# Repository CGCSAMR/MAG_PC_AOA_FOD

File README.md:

# MAG_PC_AOA_FOD
 Magnetometer, Particle Counter, Angle Of Arrival and FemtoSatellite deploy and implementation  for PC 104 Standard
 
 Link para llenar lista de componentes (Basado en nomenclatura del Documento Sheets.pdf y el proyecto)
 https://docs.google.com/spreadsheets/d/1CENiZx1N7Sxhc1uEzrNK5IoRTlJ-0vuplnp879NBSzI/edit?usp=sharing

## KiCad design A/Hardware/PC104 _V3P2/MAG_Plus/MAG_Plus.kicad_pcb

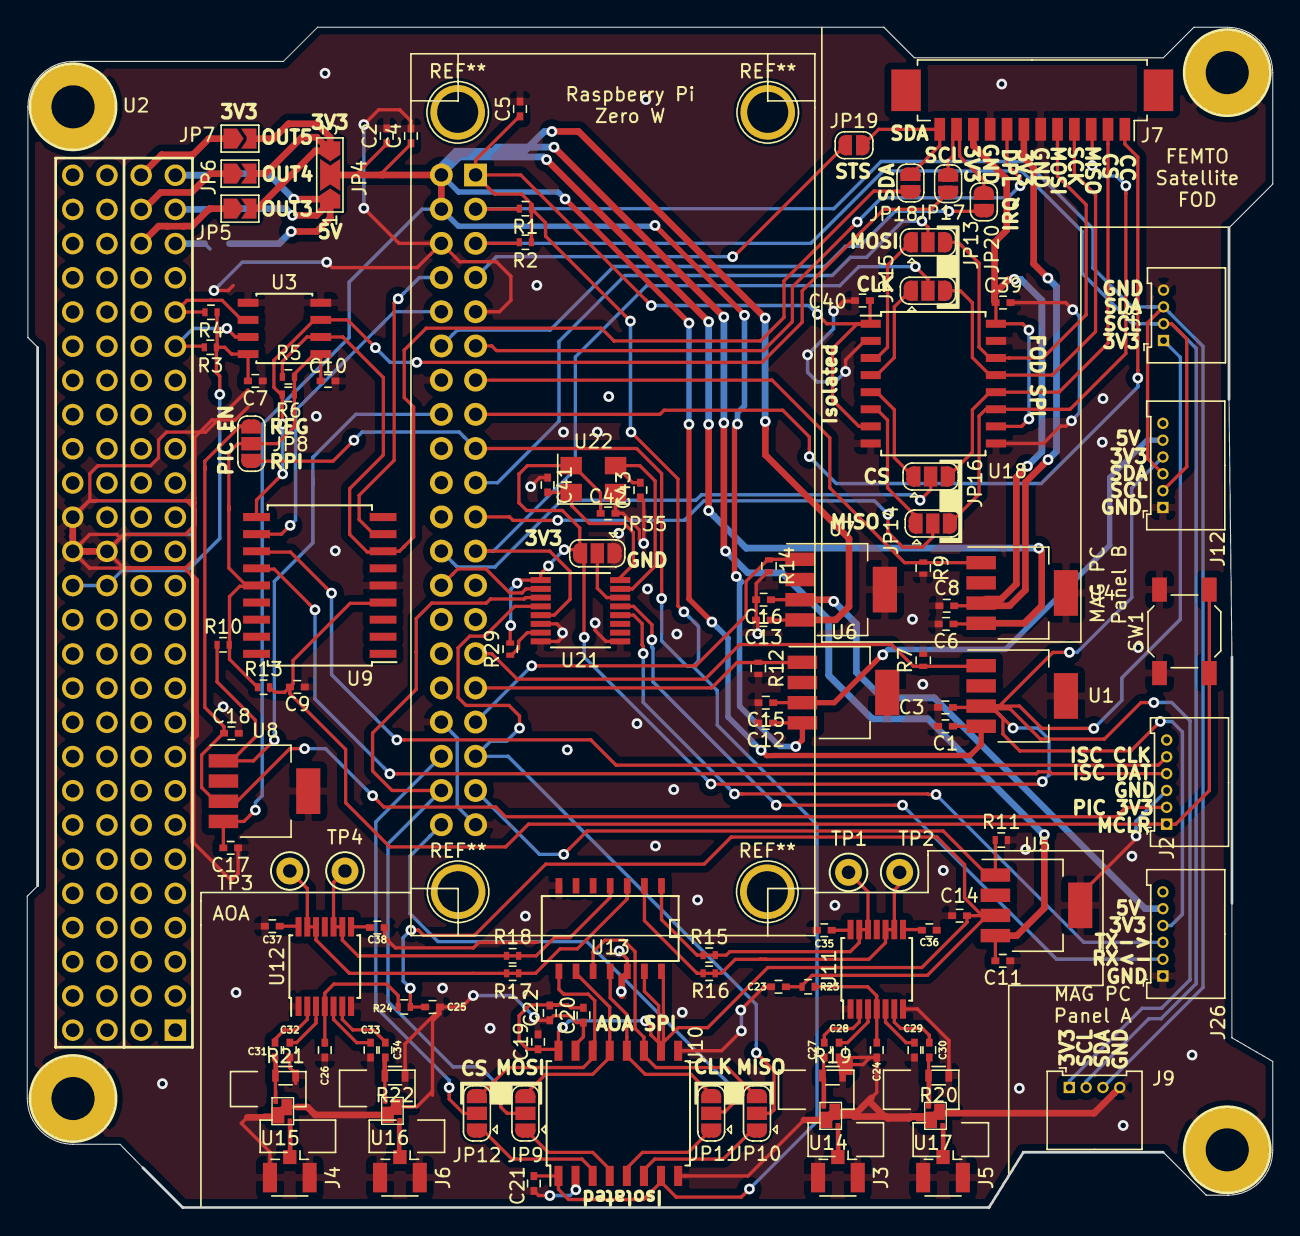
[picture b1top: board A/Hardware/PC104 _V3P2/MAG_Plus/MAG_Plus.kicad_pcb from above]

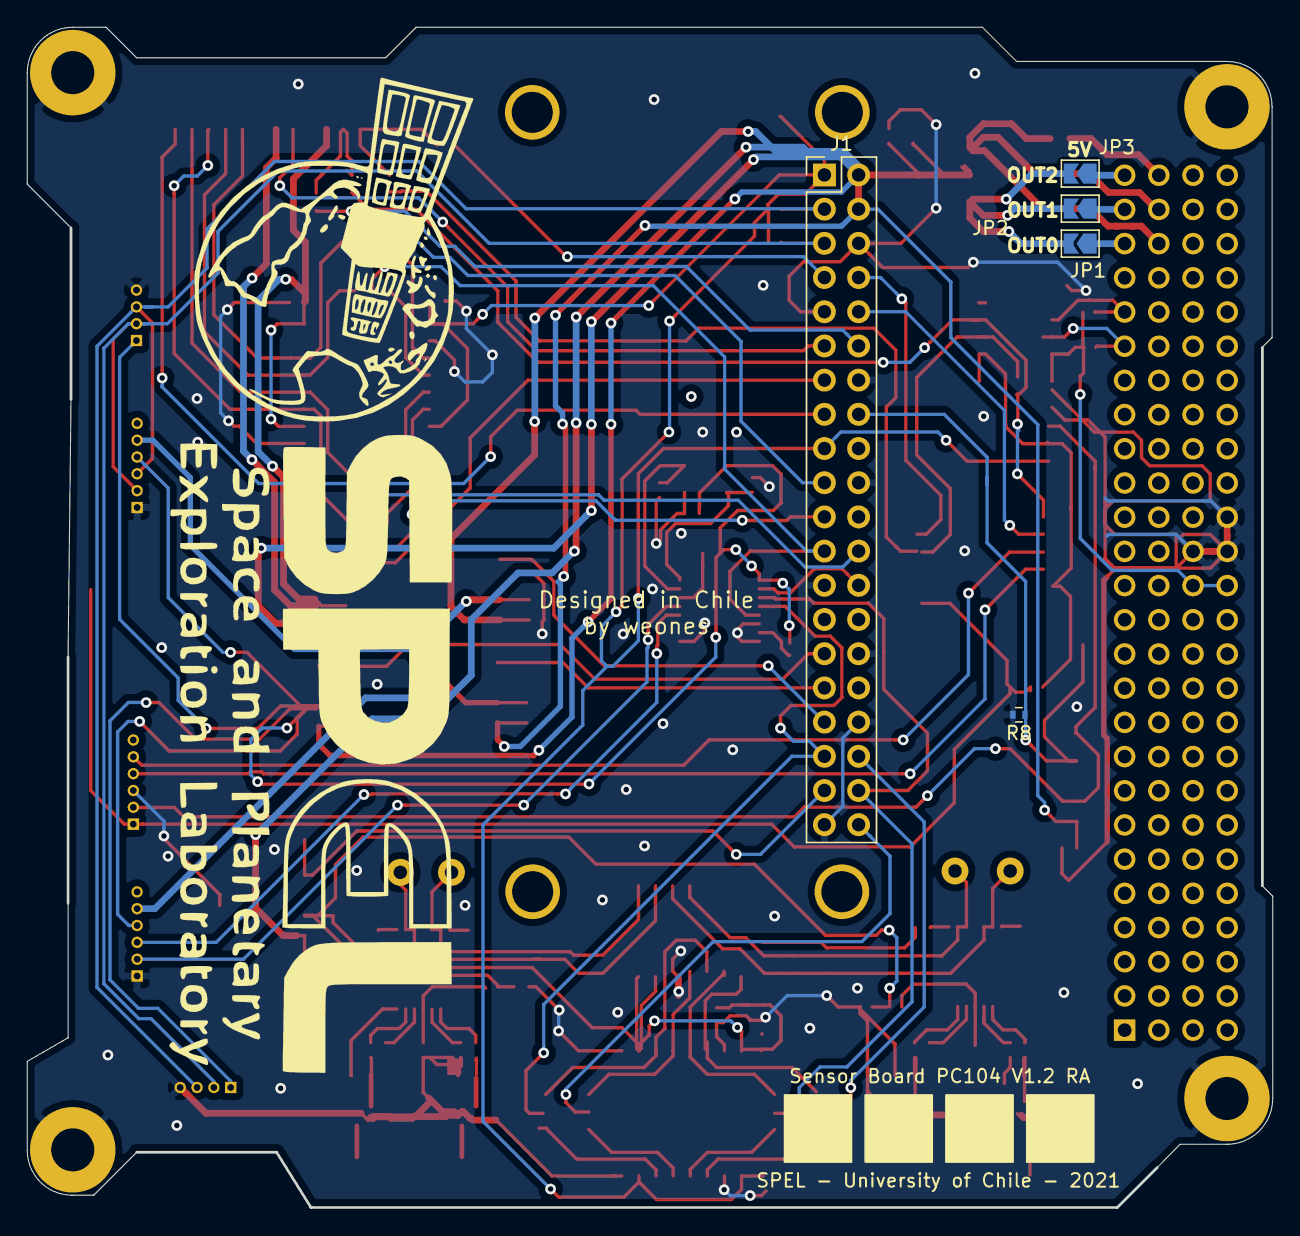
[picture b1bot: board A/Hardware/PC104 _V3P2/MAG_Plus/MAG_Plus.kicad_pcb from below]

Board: 2 copper layers, 92.5 x 87.7 mm, 125 parts (5 on the bottom side), 99 nets.

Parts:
C1, C2, C3, C4, C5, C6, C7, C8, C9, C10, C11, C12, C13, C14, C15, C16, C17, C18, C19, C20, C21, C22, C39, C40, C42: C; C_0402
C23, C24, C25, C26, C27, C28, C29, C30, C31, C32, C33, C34, C35, C36, C37, C38: C_Small; C_0402
C41, C43: 15pF; C_0402
J1: RPi_GPIO; Pin_Header_Straight_2x20_Pitch2.54mm
J2, J12, J26: Conn_01x06_Male; Molex_PicoBlade_53048-0610_06x1.25mm_Angled
J3, J4, J5, J6: U.FL-R-SMT(01); U.FL_Hirose_U.FL-R-SMT-1_Vertical
J7: Conn_01x12_Male; Molex_PicoBlade_53261-1271_12x1.25mm_Angled
J8, J9: Conn_01x04_Male; Molex_PicoBlade_53048-0410_04x1.25mm_Angled
JP1, JP2, JP3, JP5, JP6, JP7: Jumper_2_Open; SolderJumper-2_P1.3mm_Open_TrianglePad1.0x1.5mm
JP4: Jumper_3_Open; SolderJumper-3_P2.0mm_Open_TrianglePad1.0x1.5mm_NumberLabels
JP8, JP9, JP10, JP11, JP12, JP13, JP14, JP15, JP16: Jumper_3_Open; SolderJumper-3_P1.3mm_Open_RoundedPad1.0x1.5mm
JP17, JP18, JP19, JP20: Jumper_2_Open; SolderJumper-2_P1.3mm_Open_RoundedPad1.0x1.5mm
JP35: SolderJumper_3_Open; SolderJumper-3_P1.3mm_Open_RoundedPad1.0x1.5mm
R1, R2, R3, R4, R5, R6, R7, R8, R9, R10, R11, R12, R13, R14, R15, R16, R17, R18, R29: R; R_0402
R19, R20, R21, R22: R_Small; R_0603
R23, R24: R_Small; R_0402
SW1: SW_Push; SW_SPST_SKQG
TP1, TP2, TP3, TP4: TestPoint; Test_Point_Keystone_5000-5004_Miniature
U1, U4, U8: LP38693MP-3.3; SOT-223-5
U2: Payload; PC104-Standard
U3: ISO1540; SOIC-8_3.9x4.9mm_Pitch1.27mm
U5, U6, U7: LP38693MP-5.0; SOT-223-5
U9: PIC16F1847-I_SO; SOIC-18W_7.5x11.6mm_Pitch1.27mm
U10, U18: ISO7341C; SOIC-16W_7.5x10.3mm_Pitch1.27mm
U11, U12: AD8302; TSSOP-14_4.4x5mm_Pitch0.65mm
U13: MCP3204; SOIC-14_N
U14, U15, U16, U17: QPQ1906SR; QPQ1906SR3
U21: SC16IS741AIPWJ; TSSOP-16_4.4x5mm_Pitch0.65mm
U22: Xtal; Crystal_SMD_5032-4pin_5.0x3.2mm

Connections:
3V3IN: JP1.2, JP2.2, JP3.2, JP4.1
5VIN: JP4.3, JP5.2, JP6.2, JP7.2
ANT1_IN: J3.1, U14.1
ANT1_OUT: C27.1, R19.1, U14.2
ANT2_IN: J5.1, U17.1
ANT2_OUT: C30.1, R20.2, U17.2
ANT3_IN: J4.1, U15.1
ANT3_OUT: C31.1, R21.1, U15.2
ANT4_IN: J6.1, U16.1
ANT4_OUT: C34.1, R22.2, U16.2
AOA_5V: C14.1, C19.1, C20.1, C22.1, C23.2, C25.2, R23.1, R24.1, U5.3, U10.10, U10.16, U13.13, U13.14
AOA_CLK: JP11.3, U10.12, U13.11
AOA_EN: J1.37, R11.1, U5.1
AOA_MISO: JP10.3, U10.11, U13.10
AOA_MOSI: JP9.3, U10.13, U13.9
AOA_SS: JP12.3, U10.14, U13.8
CLK0: J1.23, JP15.2, U21.5
CLK1: J1.40, JP11.2
CSP_SCL: R4.2, U2.43, U3.6
CSP_SDA: R3.2, U2.41, U3.7
FOD_3V3: C8.1, C39.1, J7.7, J7.10, U4.3, U18.10, U18.16
FOD_CC: J1.15, J7.1
FOD_CS: J7.2, JP16.3, U18.12
FOD_DPL: J1.11, J7.8
FOD_EN: J1.13, R9.1, U4.1
FOD_IRQ: J1.12, JP20.1
FOD_MISO: J7.3, JP14.3, U18.11
FOD_MOSI: J7.5, JP13.3, U18.14
FOD_SCK: J7.4, JP15.3, U18.13
FOD_SCL: J7.11, JP17.2, JP20.2
FOD_SDA: J7.12, JP18.2, JP19.2
FOD_STS: J1.7, JP19.1
GND: C1.2, C2.2, C3.2, C4.2, C5.2, C6.2, C7.2, C8.2, C9.1, C10.2, C11.2, C12.2, C13.2, C14.2, C15.2, C16.2, C17.2, C18.2, C19.2, C20.2, C21.2, C22.2, C23.1, C24.1, C25.1, C26.1, C28.1, C29.1, C32.1, C33.1, C35.2, C36.2, C37.2, C38.2, C39.2, C40.2, C41.1, C42.2, C43.1, J1.6, J1.9, J1.14, J1.20, J1.25, J1.30, J1.34, J1.39, J2.3, J3.2, J4.2, J5.2, J6.2, J7.6, J7.9, J8.4, J9.4, J12.1, J26.1, JP35.1, R7.2, R8.2, R9.2, R11.2, R12.2, R14.2, R19.2, R20.1, R21.2, R22.1, SW1.1, U1.5, U2.81, U2.82, U2.84, U3.4, U3.5, U4.5, U5.5, U6.5, U7.5, U8.5, U9.5, U10.2, U10.8, U10.9, U10.15, U11.1, U11.7, U12.1, U12.7, U13.7, U13.12, U14.3, U15.3, U16.3, U17.3, U18.2, U18.8, U18.9, U18.15, U21.6, U21.8, U21.9, U22.2
ICSPCLK: J2.5, U9.12
ICSPDAT: J2.4, U9.13
IRQ: R29.1, U21.7
LP_5V: C16.1, J26.5, U7.3
LP_EN: J1.33, R14.1, U7.1
LP_RESET: JP35.2, U21.14
MAG_3V3: C3.1, C42.1, J8.1, J9.1, J12.4, J26.4, JP35.3, R29.2, U1.3, U21.1, U22.4
MAG_EN: J1.29, R7.1, U1.1
MCLR: C9.2, J2.1, R13.2, SW1.2, U9.4
MISO0: J1.21, JP14.2
MISO1: J1.35, JP10.2, U21.4
MOSI0: J1.19, JP13.2
MOSI1: J1.38, JP9.2, U21.3
unnamed: C24.2, R23.2, U11.4
unnamed: C26.2, R24.2, U12.4
unnamed: C27.2, U11.2
unnamed: C28.2, U11.3
unnamed: C29.2, U11.5
unnamed: C30.2, U11.6
unnamed: C31.2, U12.2
unnamed: C32.2, U12.3
unnamed: C33.2, U12.5
unnamed: C34.2, U12.6
unnamed: C35.1, U11.14
unnamed: C36.1, U11.8
unnamed: C37.1, U12.14
unnamed: C38.1, U12.8
OUT1_3V3: JP1.1, U2.47
OUT2_3V3: JP2.1, U2.49
OUT3_3V3: JP3.1, U2.51
OUT4_5V0: JP5.1, U2.48
OUT5_5V0: JP6.1, U2.50
OUT6_5V0: JP7.1, U2.52
PC_5V: C15.1, J12.5, U6.3
PC_EN: J1.31, R12.1, U6.1
PIC_3V3: C18.1, J2.2, JP8.1, U8.3
PIC_3V3J: C10.1, JP8.2, R5.1, R6.1, R10.2, R13.1, U3.1, U9.14
PIC_EN: J1.16, R8.1, R10.1, U8.1
PIC_SCL: JP17.1, R6.2, U3.3, U9.10
PIC_SDA: JP18.1, R5.2, U3.2, U9.7
RPI_3V3: C5.1, C21.1, C40.1, J1.1, J1.17, JP8.3, R1.1, R2.1, U10.1, U10.7, U18.1, U18.7
RPI_RX: J1.10, U9.11
RPI_SCL: J1.5, J8.2, J9.2, J12.2, R2.2
RPI_SDA: J1.3, J8.3, J9.3, J12.3, R1.2
RPI_TX: J1.8, U9.8
RX: J26.2, U21.13
SAT_3V3: C7.1, R3.1, R4.1, U2.79, U2.80, U3.8
SS00: J1.24, JP16.2
SS01: J1.26, U21.2
SS10: J1.36, JP12.2
TX: J26.3, U21.12
VIN: C1.1, C2.1, C4.1, C6.1, C11.1, C12.1, C13.1, C17.1, J1.2, J1.4, JP4.2, U1.4, U4.4, U5.4, U6.4, U7.4, U8.4
VMAG1: R15.1, R15.2, TP1.1, U11.12, U11.13, U13.1
VMAG2: R17.1, R17.2, TP3.1, U12.12, U12.13, U13.3
VPHS1: R16.1, R16.2, TP2.1, U11.9, U11.10, U13.2
VPHS2: R18.1, R18.2, TP4.1, U12.9, U12.10, U13.4
XTAL1: C43.2, U22.3
XTAL2: C41.2, U22.1
iaRPI_CLK: JP11.1, U10.5
iaRPI_MISO: JP10.1, U10.6
iaRPI_MOSI: JP9.1, U10.4
iaRPI_SS0: JP12.1, U10.3
ifRPI_CLK: JP15.1, U18.4
ifRPI_MISO: JP14.1, U18.6
ifRPI_MOSI: JP13.1, U18.3
ifRPI_SS0: JP16.1, U18.5

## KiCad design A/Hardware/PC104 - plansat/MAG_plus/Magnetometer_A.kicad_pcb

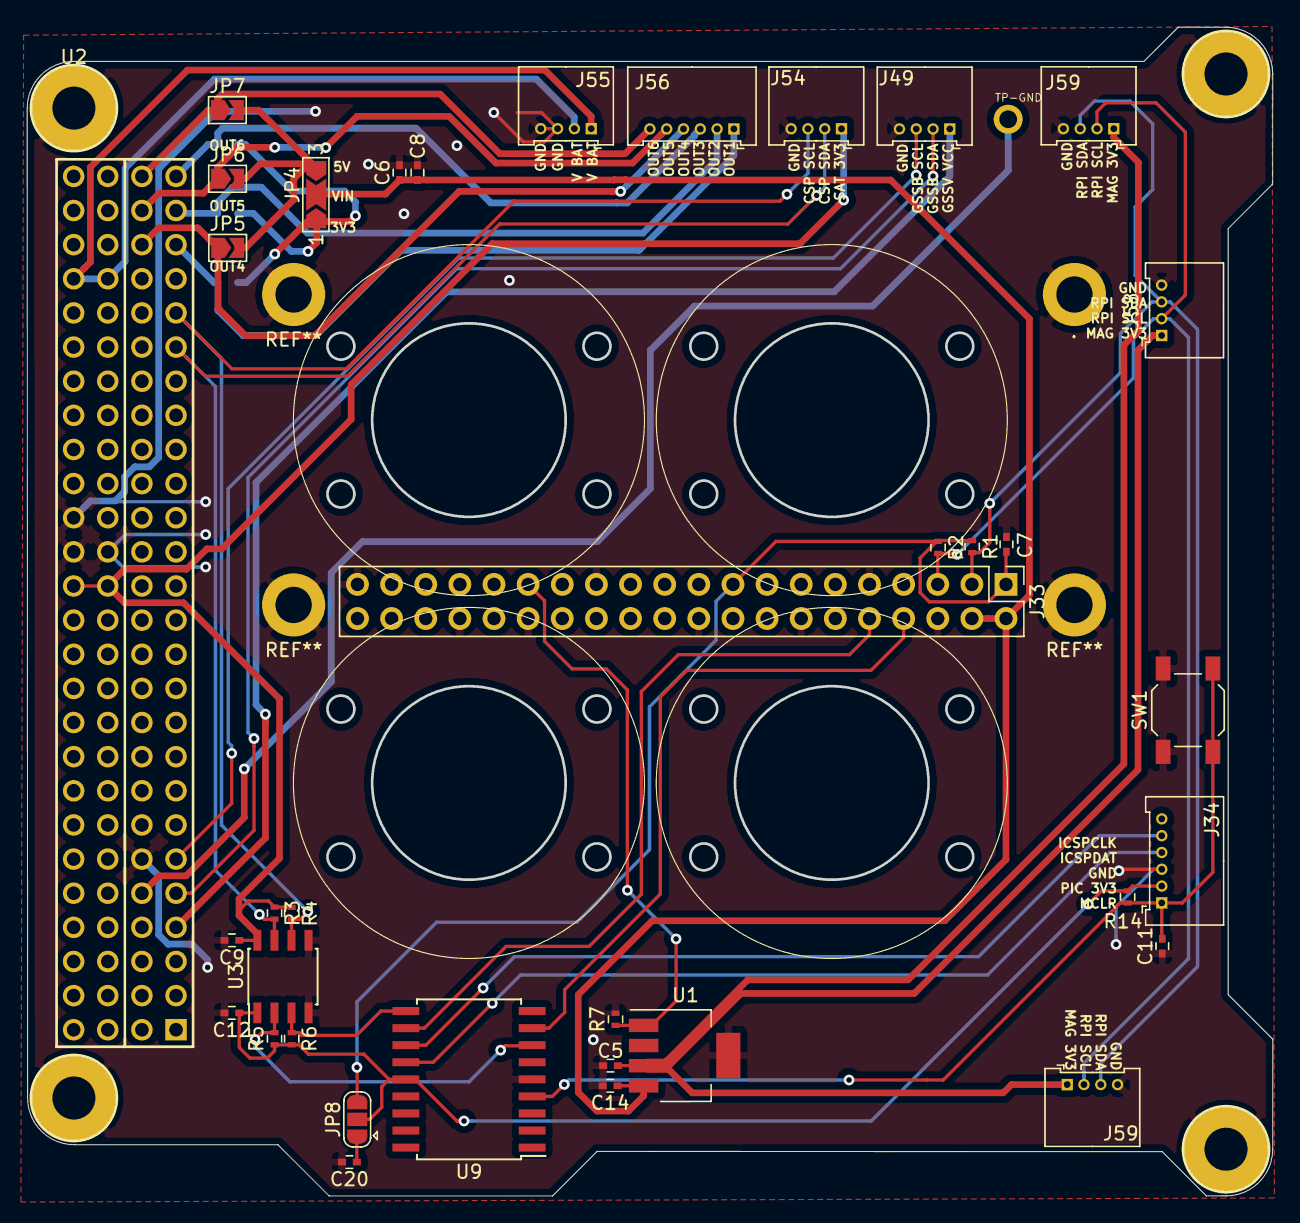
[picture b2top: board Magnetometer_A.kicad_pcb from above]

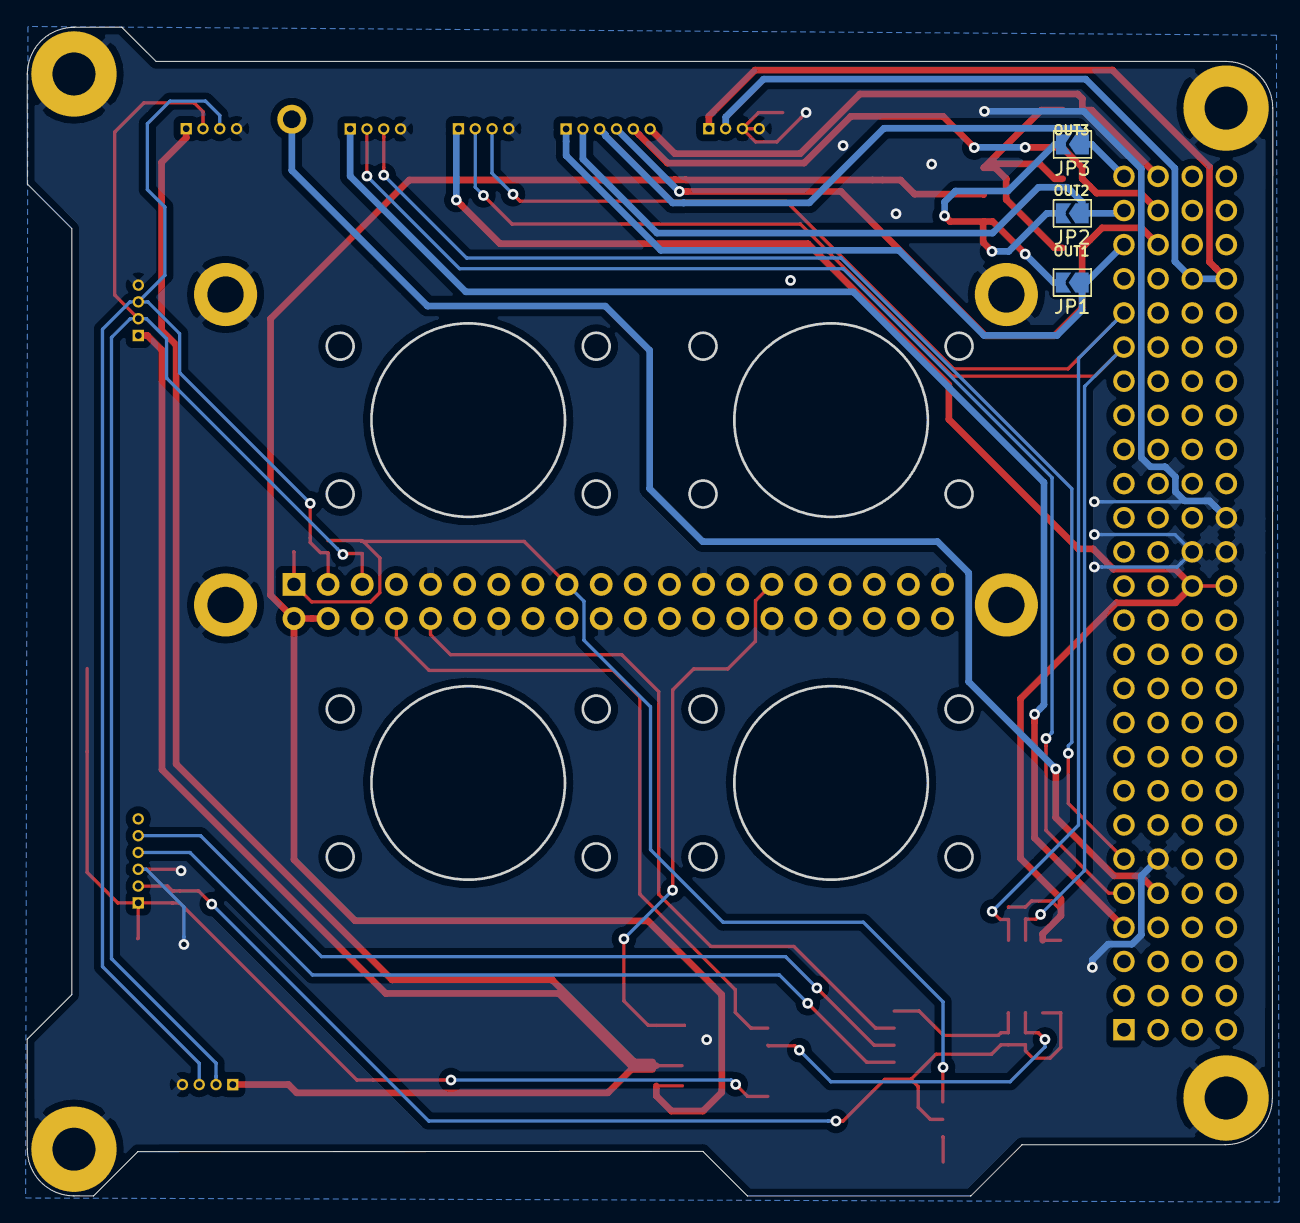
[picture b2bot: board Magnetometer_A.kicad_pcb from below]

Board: 2 copper layers, 92.7 x 87.0 mm, 41 parts (3 on the bottom side), 32 nets.

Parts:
.: MountingHole_2.7mm_M2.5_DIN965_Pad
C5, C6, C7, C8, C9, C11, C12, C14, C20: C; C_0402
J33: RPi_GPIO; Pin_Header_Straight_2x20_Pitch2.54mm
J34: Conn_01x06_Male; Molex_PicoBlade_53048-0610_06x1.25mm_Angled
J49, J54, J55: Conn_01x04_Female; Molex_PicoBlade_53048-0410_04x1.25mm_Angled
J56: Conn_01x06_Female; Molex_PicoBlade_53048-0610_06x1.25mm_Angled
J58, J59, J59#2: Conn_01x04_Male; Molex_PicoBlade_53048-0410_04x1.25mm_Angled
JP1, JP2, JP3, JP5, JP6, JP7: Jumper_2_Open; SolderJumper-2_P1.3mm_Open_TrianglePad1.0x1.5mm
JP4: Jumper_3_Open; SolderJumper-3_P2.0mm_Open_TrianglePad1.0x1.5mm_NumberLabels
JP8: Jumper_3_Open; SolderJumper-3_P1.3mm_Open_RoundedPad1.0x1.5mm
R1, R2, R3, R4, R5, R6, R7, R14: R; R_0402
SW1: SW_Push; SW_SPST_SKQG
TP-GND: PTR1PAD1-13; P1-13
U1: LP38693MP-3.3; SOT-223-5
U2: Payload; PC104-Standard
U3: ISO1540; SOIC-8_3.9x4.9mm_Pitch1.27mm
U9: PIC16F1847-I_SO; SOIC-18W_7.5x11.6mm_Pitch1.27mm

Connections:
3V3IN: JP1.2, JP2.2, JP3.2, JP4.1
5VIN: JP4.3, JP5.2, JP6.2, JP7.2
CSP_SCL: J54.3, R4.2, U2.43, U3.6
CSP_SDA: J54.2, R3.2, U2.41, U3.7
GND: ..1, C5.2, C6.2, C7.2, C8.2, C9.2, C11.1, C12.2, C14.2, C20.2, J33.6, J33.9, J33.14, J33.20, J33.25, J33.30, J33.34, J33.39, J34.3, J49.4, J54.4, J55.3, J55.4, J58.4, J59.4, J59#2.4, R7.2, SW1.1, U1.5, U2.12, U2.81, U2.82, U2.84, U3.4, U3.5, U9.5
GSSB_SCL: J49.3, U2.11
GSSB_SDA: J49.2, U2.9
GSSB_VCC: J49.1, U2.7
ICSPCLK: J34.5, U9.12
ICSPDAT: J34.4, U9.13
MAG_3V3: C5.1, J58.1, J59.1, J59#2.1, U1.3
MAG_EN: J33.29, R7.1, U1.1
MCLR: C11.2, J34.1, R14.2, SW1.2, U9.4
unnamed: TP-GND.TP, U2.10
OUT1_3V3: J56.1, JP1.1, U2.47
OUT2_3V3: J56.2, JP2.1, U2.49
OUT3_3V3: J56.3, JP3.1, U2.51
OUT4_5V0: J56.4, JP5.1, U2.48
OUT5_5V0: J56.5, JP6.1, U2.50
OUT6_5V0: J56.6, JP7.1, U2.52
PIC_3V3: C20.1, JP8.1
PIC_3V3J: C12.1, J34.2, JP8.2, R5.1, R6.1, R14.1, U3.1, U9.14
PIC_SCL: R6.2, U3.3, U9.10
PIC_SDA: R5.2, U3.2, U9.7
RPI_3V3: C7.1, J33.1, J33.17, JP8.3, R1.1, R2.1
RPI_RX: J33.10, U9.11
RPI_SCL: J33.5, J58.2, J59.2, J59#2.2, R2.2
RPI_SDA: J33.3, J58.3, J59.3, J59#2.3, R1.2
RPI_TX: J33.8, U9.8
SAT_3V3: C9.1, J54.1, R3.1, R4.1, U2.79, U2.80, U3.8
VIN: C6.1, C8.1, C14.1, J33.2, J33.4, JP4.2, U1.4
V_BAT: J55.1, J55.2, U2.97, U2.98

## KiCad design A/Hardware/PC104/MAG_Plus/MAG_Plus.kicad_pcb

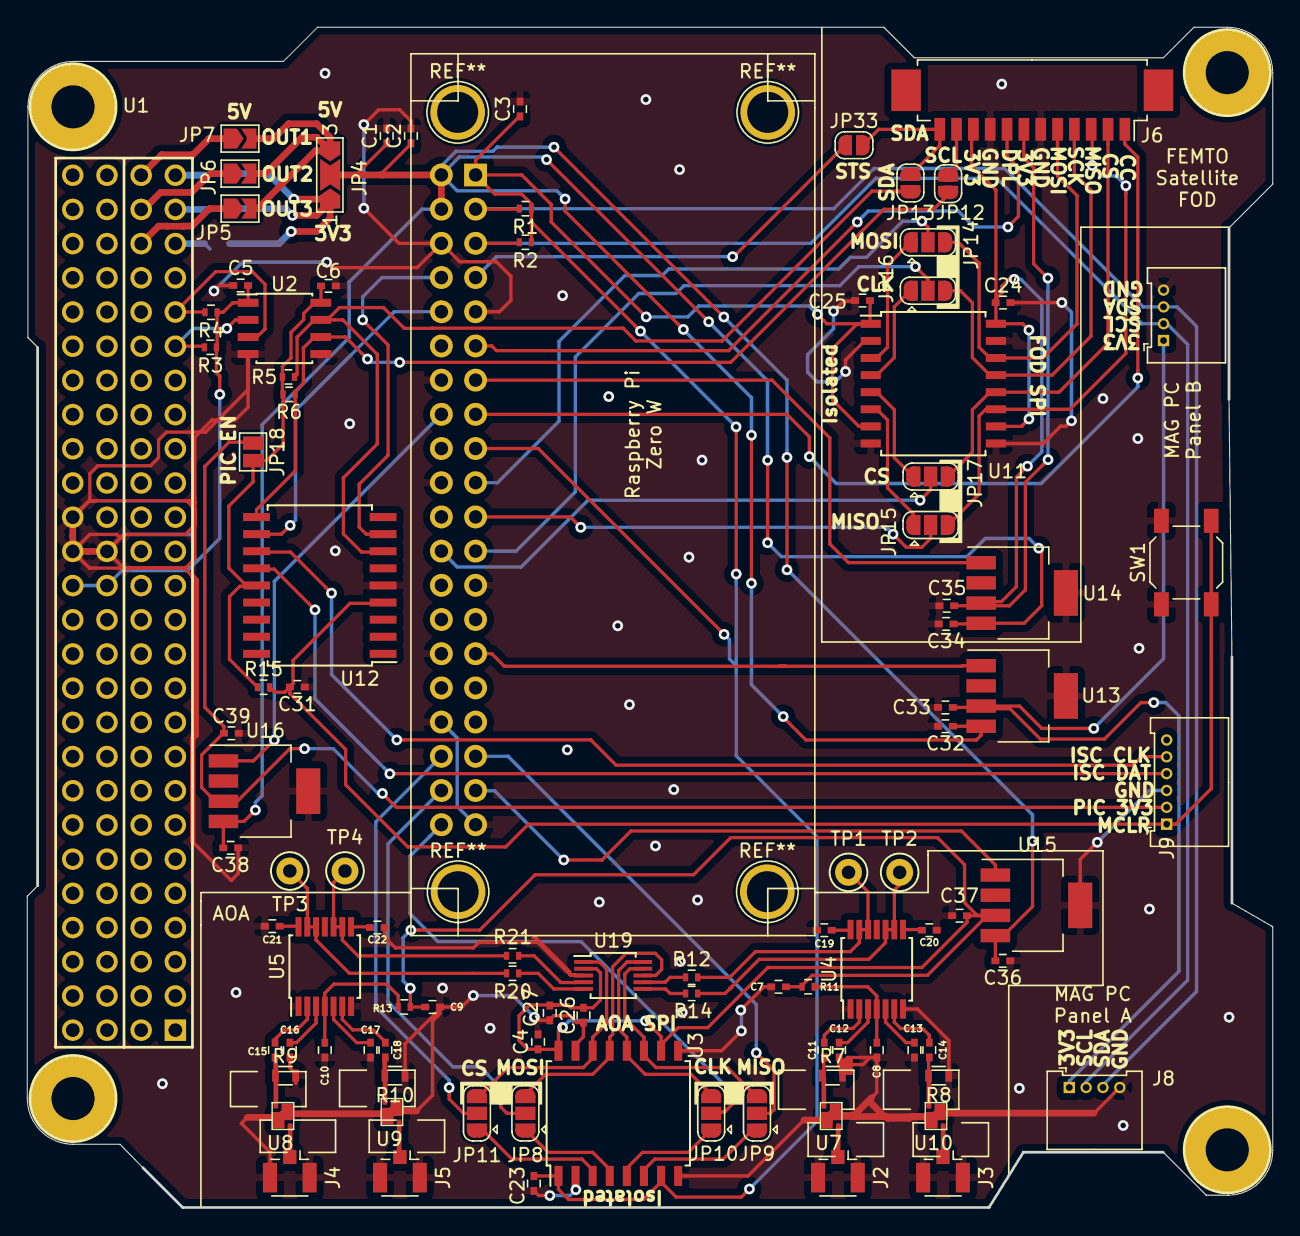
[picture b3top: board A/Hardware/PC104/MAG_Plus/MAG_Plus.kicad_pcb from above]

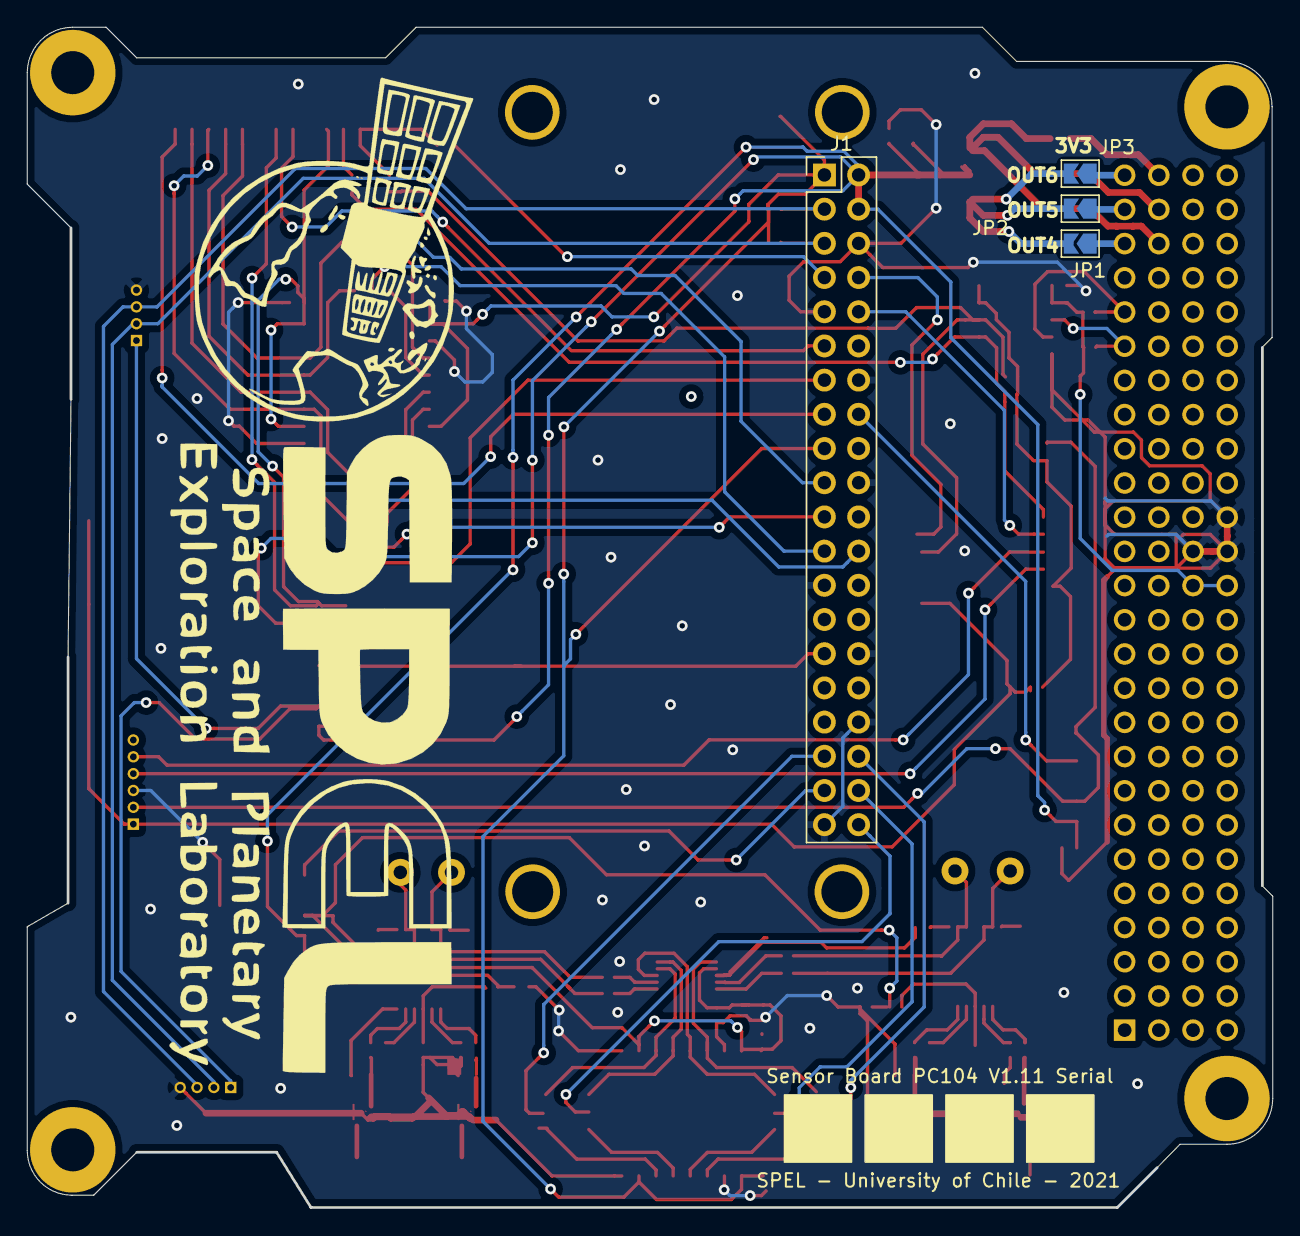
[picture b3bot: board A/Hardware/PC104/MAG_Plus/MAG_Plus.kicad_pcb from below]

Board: 2 copper layers, 92.5 x 87.7 mm, 102 parts (4 on the bottom side), 91 nets.

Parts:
C1, C2, C3, C4, C5, C6, C23, C24, C25, C26, C27, C31, C32, C33, C34, C35, C36, C37, C38, C39: C; C_0402
C7, C8, C9, C10, C11, C12, C13, C14, C15, C16, C17, C18, C19, C20, C21, C22: C_Small; C_0402
J1: RPi_GPIO; Pin_Header_Straight_2x20_Pitch2.54mm
J2, J3, J4, J5: U.FL-R-SMT(01); U.FL_Hirose_U.FL-R-SMT-1_Vertical
J6: Conn_01x12_Male; Molex_PicoBlade_53261-1271_12x1.25mm_Angled
J7, J8: Conn_01x04_Male; Molex_PicoBlade_53048-0410_04x1.25mm_Angled
J9: Conn_01x06_Male; Molex_PicoBlade_53048-0610_06x1.25mm_Angled
JP1, JP2, JP3, JP5, JP6, JP7: Jumper_2_Open; SolderJumper-2_P1.3mm_Open_TrianglePad1.0x1.5mm
JP4: Jumper_3_Open; SolderJumper-3_P2.0mm_Open_TrianglePad1.0x1.5mm_NumberLabels
JP8, JP9, JP10, JP11, JP14, JP15, JP16, JP17: Jumper_3_Open; SolderJumper-3_P1.3mm_Open_RoundedPad1.0x1.5mm
JP12, JP13, JP33: Jumper_2_Open; SolderJumper-2_P1.3mm_Open_RoundedPad1.0x1.5mm
JP18: Jumper_2_Open; SolderJumper-2_P1.3mm_Open_Pad1.0x1.5mm
R1, R2, R3, R4, R5, R6, R12, R14, R15, R20, R21: R; R_0402
R7, R8, R9, R10: R_Small; R_0603
R11, R13: R_Small; R_0402
SW1: SW_Push; SW_SPST_SKQG
TP1, TP2, TP3, TP4: TestPoint; Test_Point_Keystone_5000-5004_Miniature
U1: Payload; PC104-Standard
U2: ISO1540; SOIC-8_3.9x4.9mm_Pitch1.27mm
U3, U11: ISO7341C; SOIC-16W_7.5x10.3mm_Pitch1.27mm
U4, U5: AD8302; TSSOP-14_4.4x5mm_Pitch0.65mm
U7, U8, U9, U10: QPQ1906SR; QPQ1906SR2
U12: PIC16F1847-I_SO; SOIC-18W_7.5x11.6mm_Pitch1.27mm
U13, U14, U16: LP38693MP-3.3; SOT-223-5
U15: LP38693MP-5.0; SOT-223-5
U19: ADC084S051; MSOP-10_3x3mm_Pitch0.5mm

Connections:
3V3IN: JP1.2, JP2.2, JP3.2, JP4.1
5VIN: JP4.3, JP5.2, JP6.2, JP7.2
ANT1_IN: J2.1, U7.1
ANT1_OUT: C11.1, R7.1, U7.2
ANT2_IN: J3.1, U10.1
ANT2_OUT: C14.1, R8.2, U10.2
ANT3_IN: J4.1, U8.1
ANT3_OUT: C15.1, R9.1, U8.2
ANT4_IN: J5.1, U9.1
ANT4_OUT: C18.1, R10.2, U9.2
AOA_5V: C4.1, C7.2, C9.2, C26.1, C27.1, C37.1, R11.1, R13.1, U3.10, U3.16, U15.3, U19.2
AOA_CLK: JP10.3, U3.12, U19.10
AOA_EN: J1.37, U15.1
AOA_MISO: JP9.3, U3.11, U19.9
AOA_MOSI: JP8.3, U3.13, U19.8
AOA_SS: JP11.3, U3.14, U19.1
CLK0: J1.23, JP16.2
CLK1: J1.40, JP10.2
CSP_SCL: R4.2, U1.43, U2.3
CSP_SDA: R3.2, U1.41, U2.2
FOD_3V3: C24.1, C35.1, J6.7, J6.10, U11.10, U11.16, U14.3
FOD_CC: J1.15, J6.1
FOD_CS: J6.2, JP17.3, U11.12
FOD_DPL: J1.11, J6.8
FOD_EN: J1.13, U14.1
FOD_MISO: J6.3, JP15.3, U11.11
FOD_MOSI: J6.5, JP14.3, U11.14
FOD_SCK: J6.4, JP16.3, U11.13
FOD_SCL: J6.11, JP12.2
FOD_SDA: J6.12, JP13.2, JP33.2
FOD_STS: J1.7, JP33.1
GND: C1.2, C2.2, C3.2, C4.2, C5.2, C6.2, C7.1, C8.1, C9.1, C10.1, C12.1, C13.1, C16.1, C17.1, C19.2, C20.2, C21.2, C22.2, C23.2, C24.2, C25.2, C26.2, C27.2, C31.1, C32.2, C33.2, C34.2, C35.2, C36.2, C37.2, C38.2, C39.2, J1.6, J1.9, J1.14, J1.20, J1.25, J1.30, J1.34, J1.39, J2.2, J3.2, J4.2, J5.2, J6.6, J6.9, J7.4, J8.4, J9.3, R7.2, R8.1, R9.2, R10.1, SW1.1, U1.81, U1.82, U1.84, U2.4, U2.5, U3.2, U3.8, U3.9, U3.15, U4.1, U4.7, U5.1, U5.7, U7.3, U8.3, U9.3, U10.3, U11.2, U11.8, U11.9, U11.15, U12.5, U13.5, U14.5, U15.5, U16.5, U19.3
ICSPCLK: J9.5, U12.12
ICSPDAT: J9.4, U12.13
MAG_3V3: C33.1, J7.1, J8.1, U13.3
MAG_EN: J1.29, U13.1
MCLR: C31.2, J9.1, R15.2, SW1.2, U12.4
MISO0: J1.21, JP15.2
MISO1: J1.35, JP9.2
MOSI0: J1.19, JP14.2
MOSI1: J1.38, JP8.2
unnamed: C8.2, R11.2, U4.4
unnamed: C10.2, R13.2, U5.4
unnamed: C11.2, U4.2
unnamed: C12.2, U4.3
unnamed: C13.2, U4.5
unnamed: C14.2, U4.6
unnamed: C15.2, U5.2
unnamed: C16.2, U5.3
unnamed: C17.2, U5.5
unnamed: C18.2, U5.6
unnamed: C19.1, U4.14
unnamed: C20.1, U4.8
unnamed: C21.1, U5.14
unnamed: C22.1, U5.8
OUT1_3V3: JP1.1, U1.47
OUT2_3V3: JP2.1, U1.49
OUT3_3V3: JP3.1, U1.51
OUT4_5V0: JP5.1, U1.48
OUT5_5V0: JP6.1, U1.50
OUT6_5V0: JP7.1, U1.52
PIC_3V3: C39.1, J9.2, JP18.1, U16.3
PIC_3V3J: C6.1, JP18.2, R5.1, R6.1, R15.1, U2.8, U12.14
PIC_EN: J1.16, U16.1
PIC_SCL: JP12.1, R6.2, U2.6, U12.10
PIC_SDA: JP13.1, R5.2, U2.7, U12.7
RPI_3V3: C3.1, C23.1, C25.1, J1.1, J1.17, R1.1, R2.1, U3.1, U3.7, U11.1, U11.7
RPI_RX: J1.10, U12.11
RPI_SCL: J1.5, J7.2, J8.2, R2.2
RPI_SDA: J1.3, J7.3, J8.3, R1.2
RPI_TX: J1.8, U12.8
SAT_3V3: C5.1, R3.1, R4.1, U1.79, U1.80, U2.1
SS00: J1.24, JP17.2
SS10: J1.36, JP11.2
VIN: C1.1, C2.1, C32.1, C34.1, C36.1, C38.1, J1.2, J1.4, JP4.2, U13.4, U14.4, U15.4, U16.4
VMAG1: R12.2, TP1.1, U4.12, U4.13
VMAG1A: R12.1, U19.7
VMAG2: R20.2, TP3.1, U5.12, U5.13
VMAG2A: R20.1, U19.5
VPHS1: R14.2, TP2.1, U4.9, U4.10
VPHS1A: R14.1, U19.6
VPHS2: R21.2, TP4.1, U5.9, U5.10
VPHS2A: R21.1, U19.4
iaRPI_CLK: JP10.1, U3.5
iaRPI_MISO: JP9.1, U3.6
iaRPI_MOSI: JP8.1, U3.4
iaRPI_SS0: JP11.1, U3.3
ifRPI_CLK: JP16.1, U11.4
ifRPI_MISO: JP15.1, U11.6
ifRPI_MOSI: JP14.1, U11.3
ifRPI_SS0: JP17.1, U11.5

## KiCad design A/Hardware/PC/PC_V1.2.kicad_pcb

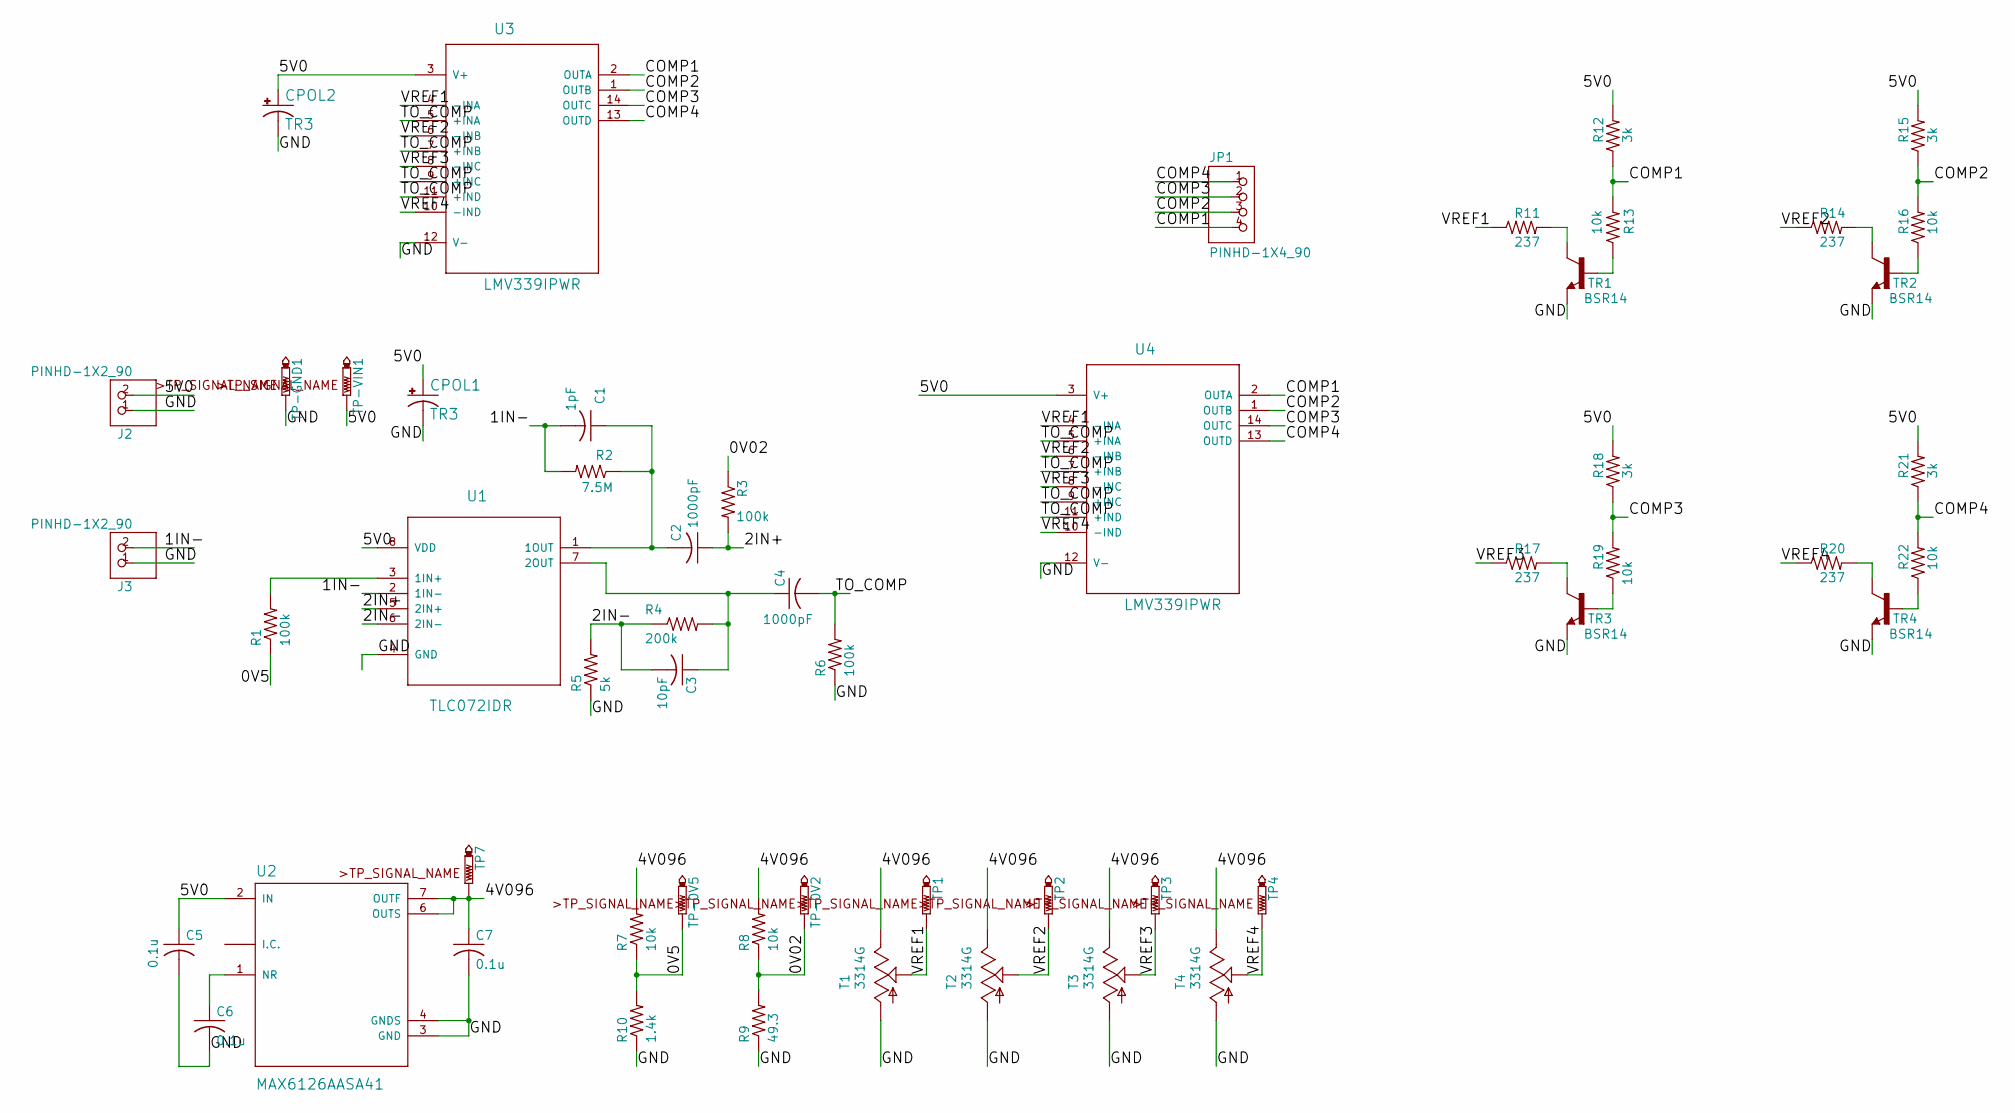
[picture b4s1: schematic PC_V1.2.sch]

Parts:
C1: 1pF; C0402
C2, C4: 1000pF; C0603
C3: 10pF; C0603
C5, C6, C7: 0.1u; C0402
CPOL1, CPOL2: TR3; EIA3528
J2, J3: PINHD-1X2_90; 1X02_90
JP1: PINHD-1X4_90; 1X04_90
R1, R3, R6: 100k; R0603
R2: 7.5M; R1206
R4: 200k; R0603
R5: 5k; R0402
R7, R8, R13, R16, R19, R22: 10k; R0603
R9: 49.3; R0603
R10: 1.4k; R0402
R11, R14, R17, R20: 237; R0603
R12, R15, R18, R21: 3k; R0603
T1, T2, T3, T4: 3314G
TP1, TP2, TP3, TP4, TP7: PTR1PAD1-13; P1-13
TP-0V2, TP-0V5: PTR1PAD1-13; P1-13
TP-GND1: PTR1PAD1-13; P1-13
TP-VIN1: PTR1PAD1-13; P1-13
TR1, TR2, TR3, TR4: BSR14; SOT95P240X120-3N
U1: TLC072IDR; SOIC127P600X175-8N
U2: MAX6126AASA41; SOIC127P600X175-8N
U3: LMV339IPWR; SOP65P640X110-14N
U4: LMV339IPWR; DIP-14_W7.62mm

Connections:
/0V02: R3.1, R8.1, R9.2, TP-0V2.TP
/0V5: R1.1, R7.1, R10.2, TP-0V5.TP
/1IN-: C1.2, J3.2, R2.2, U1.2 (1IN-)
/2IN+: C2.1, R3.2, U1.5 (2IN+)
/2IN-: C3.2, R4.1, R5.2, U1.6 (2IN-)
/4V096: C7.1, R7.2, R8.2, T1.3, T2.3, T3.3, T4.3, TP7.TP, U2.6 (OUTS), U2.7 (OUTF)
/5V0: C5.1, CPOL1.A (+), CPOL2.A (+), J2.2, R12.2, R15.2, R18.2, R21.2, TP-VIN1.TP, U1.8 (VDD), U2.2 (IN), U3.3 (V+), U4.3 (V+)
/COMP1: JP1.4, R12.1, R13.2, U3.2 (OUTA), U4.2 (OUTA)
/COMP2: JP1.3, R15.1, R16.2, U3.1 (OUTB), U4.1 (OUTB)
/COMP3: JP1.2, R18.1, R19.2, U3.14 (OUTC), U4.14 (OUTC)
/COMP4: JP1.1, R21.1, R22.2, U3.13 (OUTD), U4.13 (OUTD)
/GND: C5.2, C6.2, C7.2, CPOL1.C (-), CPOL2.C (-), J2.1, J3.1, R5.1, R6.1, R9.1, R10.1, T1.1, T2.1, T3.1, T4.1, TP-GND1.TP, TR1.2 (E), TR2.2 (E), TR3.2 (E), TR4.2 (E), U1.4 (GND), U2.3 (GND), U2.4 (GNDS), U3.12 (V-), U4.12 (V-)
/TO_COMP: C4.2, R6.2, U3.5 (+INA), U3.7 (+INB), U3.9 (+INC), U3.11 (+IND), U4.5 (+INA), U4.7 (+INB), U4.9 (+INC), U4.11 (+IND)
/VREF1: R11.1, T1.2, TP1.TP, U3.4 (-INA), U4.4 (-INA)
/VREF2: R14.1, T2.2, TP2.TP, U3.6 (-INB), U4.6 (-INB)
/VREF3: R17.1, T3.2, TP3.TP, U3.8 (-INC), U4.8 (-INC)
/VREF4: R20.1, T4.2, TP4.TP, U3.10 (-IND), U4.10 (-IND)
unnamed: C1.1, C2.2, R2.1, U1.1 (1OUT)
unnamed: C3.1, C4.1, R4.2, U1.7 (2OUT)
unnamed: C6.1, U2.1 (NR)
unnamed: R1.2, U1.3 (1IN+)
unnamed: R11.2, TR1.3 (C)
unnamed: R13.1, TR1.1 (B)
unnamed: R14.2, TR2.3 (C)
unnamed: R16.1, TR2.1 (B)
unnamed: R17.2, TR3.3 (C)
unnamed: R19.1, TR3.1 (B)
unnamed: R20.2, TR4.3 (C)
unnamed: R22.1, TR4.1 (B)
unnamed: U2.5 (I.C.), U2.8 (I.C.)

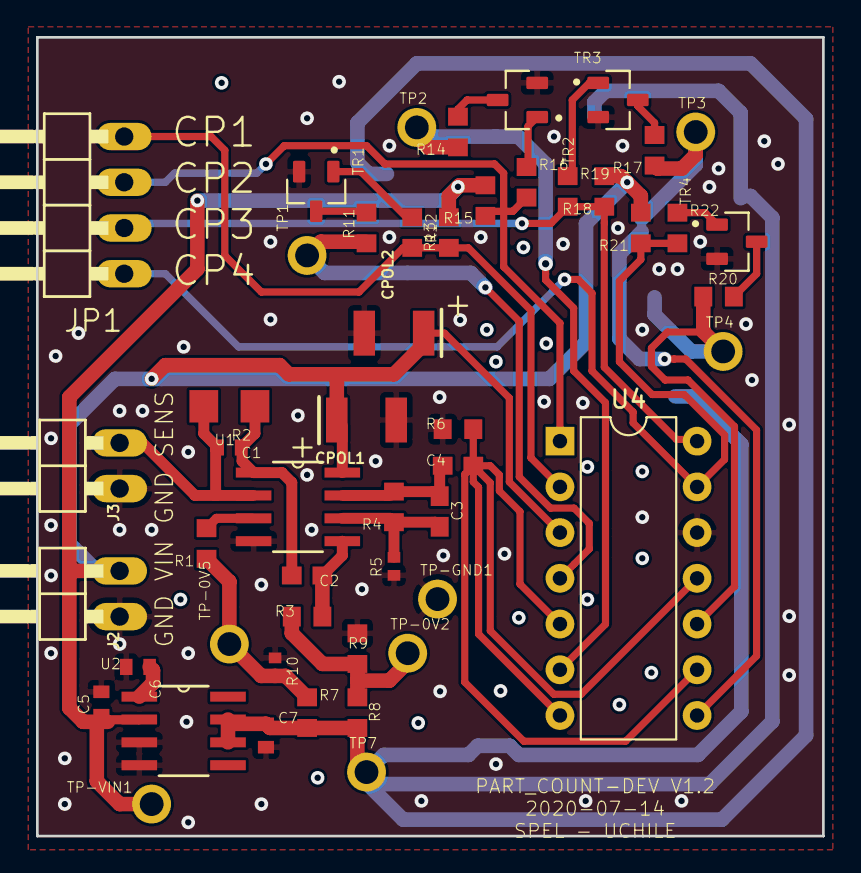
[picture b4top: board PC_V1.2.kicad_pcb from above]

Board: 2 copper layers, 43.7 x 44.4 mm, 54 parts (0 on the bottom side), 30 nets.
